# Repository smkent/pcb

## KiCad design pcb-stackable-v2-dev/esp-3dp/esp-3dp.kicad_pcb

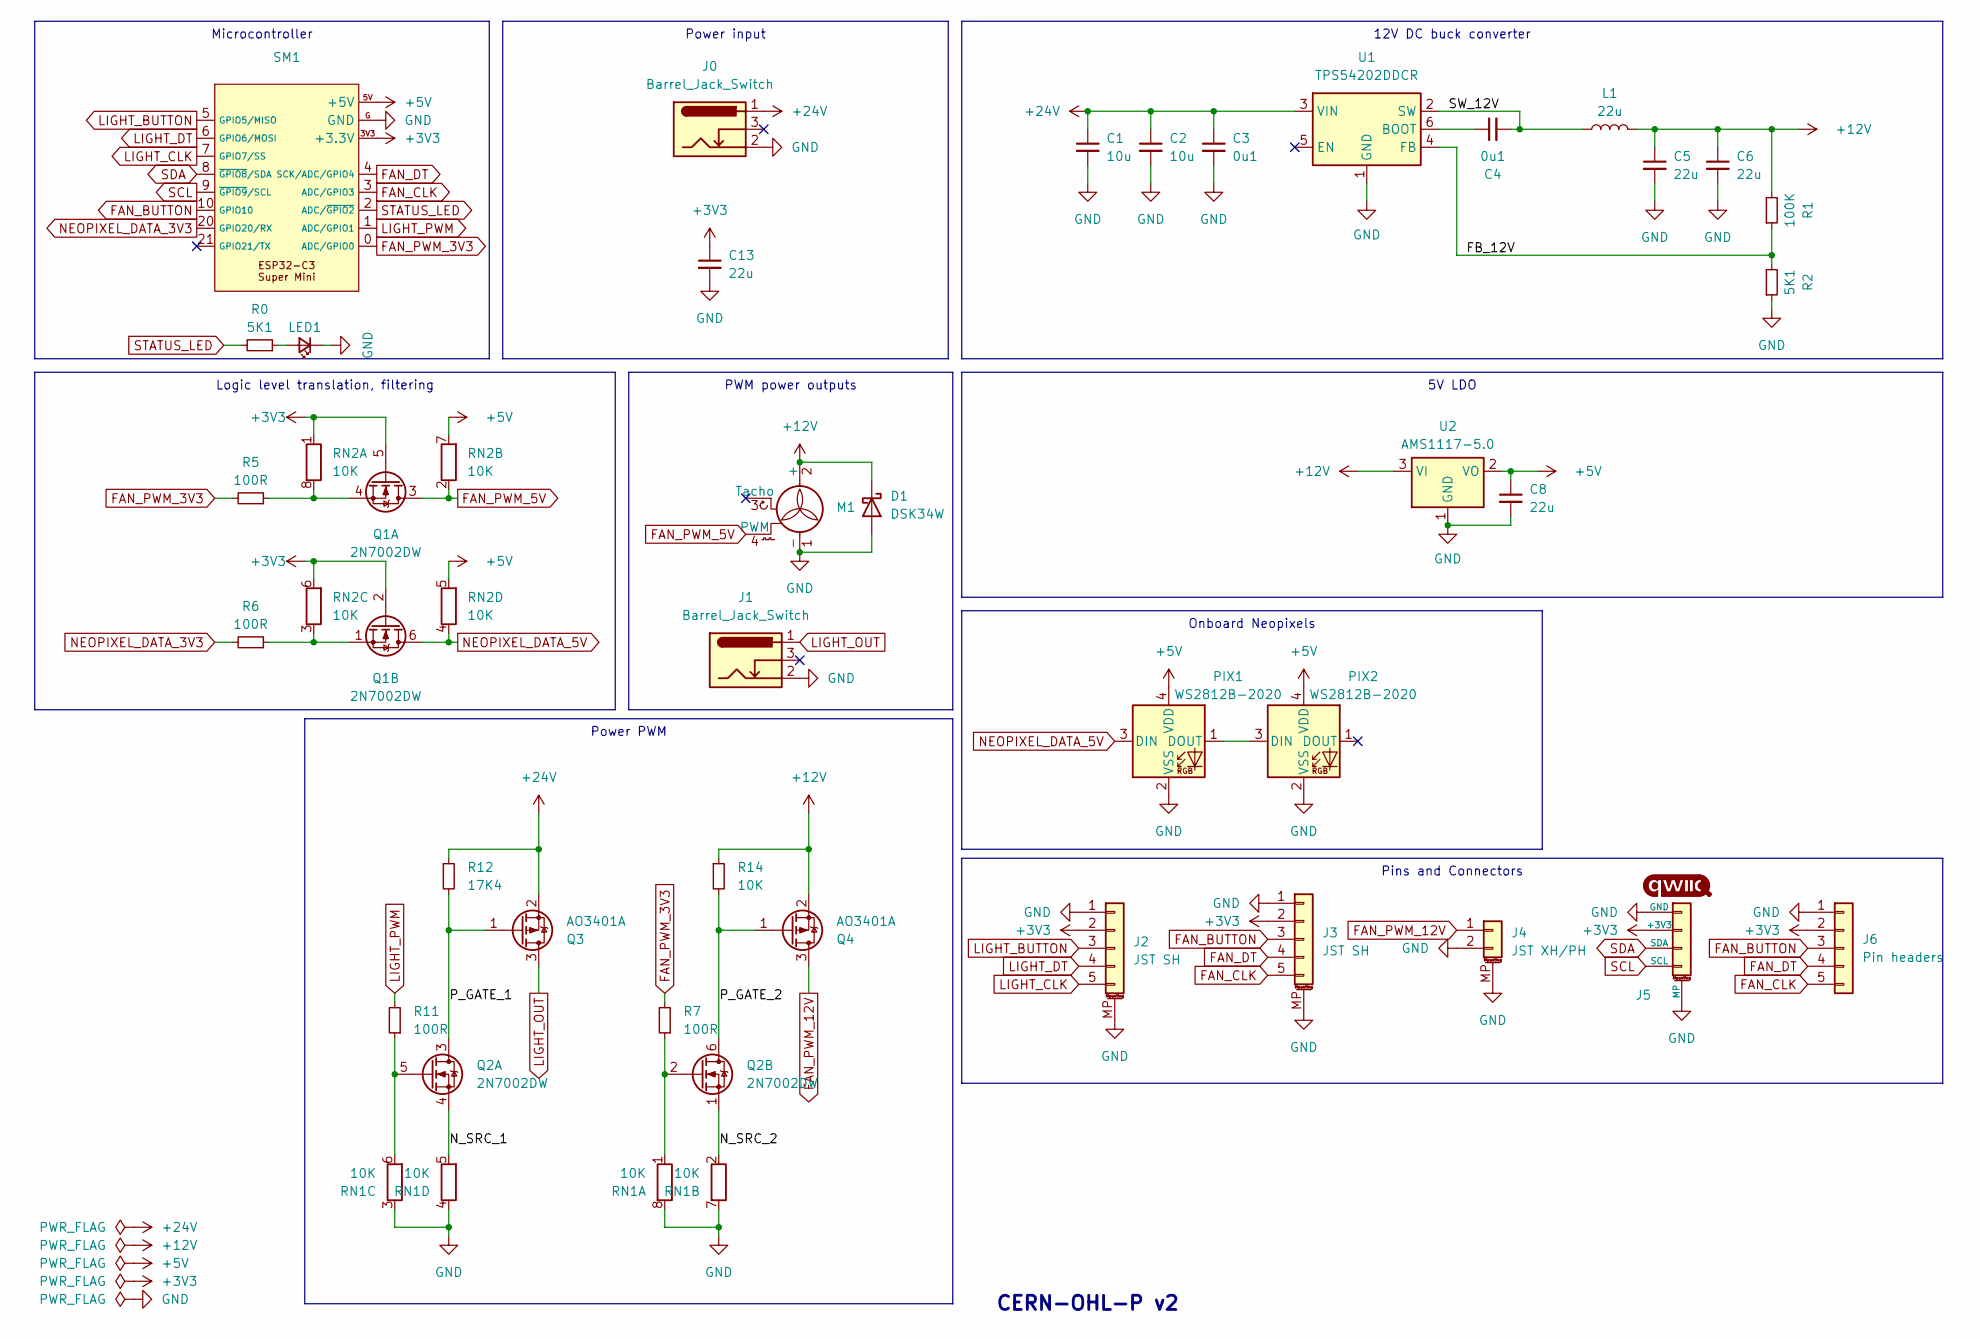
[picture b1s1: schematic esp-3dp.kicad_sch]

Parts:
C1, C2: 10u; C_0603_1608Metric_Pad1.08x0.95mm_HandSolder
C3, C4: 0u1; C_0603_1608Metric_Pad1.08x0.95mm_HandSolder
C5, C6, C8: 22u; C_0805_2012Metric_Pad1.18x1.45mm_HandSolder
C13: 22u; C_0603_1608Metric_Pad1.08x0.95mm_HandSolder
D1: DSK34W; D_SOD-123F_simple
J0, J1: Barrel_Jack_Switch; DC-IN_DC-050-2.0-BB_rev2
J2, J3: JST SH; JST_SH_SM05B-SRSS-TB_1x05-1MP_P1.00mm_Horizontal
J4: JST XH/PH; Conn_Combo_JST-1x02-XH_PH-SMD-pad2gnd
J5: Qwiic; Qwiic-SMD-horizontal-logo-bottom-pinout
J6: Pin headers; PinHeader_1x05_P2.54mm_Vertical_simple_pad1gnd
L1: 22u; IND-SMD_L7.0-W6.6; LCSC Part C22471106
LED1: LED_Small; LED_0603_1608Metric_Pad1.05x0.95mm_HandSolder_simple
M1: KF2510; FanPinHeader_1x04_P2.54mm_Horizontal
PIX1, PIX2: WS2812B-2020; LED-SMD_4P-L2.0-W2.0-BR-1
Q1, Q2: 2N7002DW; SOT-363_SC-70-6; LCSC Part C5190214
Q3, Q4: AO3401A; SOT-23
R0, R2: 5K1; R_0603_1608Metric_Pad0.98x0.95mm_HandSolder
R1: 100K; R_0603_1608Metric_Pad0.98x0.95mm_HandSolder
R5, R6, R7, R11: 100R; R_0603_1608Metric_Pad0.98x0.95mm_HandSolder
R12: 17K4; R_0603_1608Metric_Pad0.98x0.95mm_HandSolder
R14: 10K; R_0603_1608Metric_Pad0.98x0.95mm_HandSolder
RN1, RN2: 10K; R_Array_Convex_4x0603
SM1: ESP32-C3-Super-Mini-Castellated-SMD-only
U1: TPS54202DDCR; SOT-23-6; LCSC Part C191884
U2: AMS1117-5.0; SOT-223-3_TabPin2

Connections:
+3V3: C13.1, J2.2, J3.2, J5.2 (+3V3), J6.2, Q1.2 (G), Q1.5 (G), RN2.1 (R1.1), RN2.6 (R3.2), SM1.3V3 (+3.3V)
+5V: C8.1, PIX1.4 (VDD), PIX2.4 (VDD), RN2.5 (R4.2), RN2.7 (R2.2), SM1.5V (+5V), U2.2 (VO)
+12V: C5.1, C6.1, D1.1 (K), L1.2, M1.2 (+), Q4.2 (S), R1.2, R14.1, U2.3 (VI)
+24V: C1.1, C2.1, C3.1, J0.1, Q3.2 (S), R12.1, U1.3 (VIN)
/FB_12V: R1.1, R2.2, U1.4 (FB)
/N_SRC_1: Q2.4 (S), RN1.5 (R4.2)
/N_SRC_2: Q2.1 (S), RN1.2 (R2.1)
/P_GATE_1: Q2.3 (D), Q3.1 (G), R12.2
/P_GATE_2: Q2.6 (D), Q4.1 (G), R14.2
/SW_12V: C4.2, L1.1, U1.2 (SW)
FAN_BUTTON: J3.3, J6.3, SM1.10 (GPIO10)
FAN_CLK: J3.5, J6.5, SM1.3 (ADC/GPIO3)
FAN_DT: J3.4, J6.4, SM1.4 (SCK/ADC/GPIO4)
FAN_PWM_3V3: R5.2, R7.2, SM1.0 (ADC/GPIO0)
FAN_PWM_5V: M1.4 (PWM), Q1.3 (D), RN2.2 (R2.1)
FAN_PWM_12V: J4.1, Q4.3 (D)
GND: C1.2, C2.2, C3.2, C5.2, C6.2, C8.2, C13.2, D1.2 (A), J0.2, J1.2, J2.1, J2.MP (MountPin), J3.1, J3.MP (MountPin), J4.2, J4.MP (MountPin), J5.1 (GND), J5.MP, J6.1, LED1.1 (K), M1.1 (-), PIX1.2 (VSS), PIX2.2 (VSS), R2.1, RN1.3 (R3.1), RN1.4 (R4.1), RN1.7 (R2.2), RN1.8 (R1.2), SM1.G (GND), U1.1 (GND), U2.1 (GND)
LIGHT_BUTTON: J2.3, SM1.5 (GPIO5/MISO)
LIGHT_CLK: J2.5, SM1.7 (GPIO7/SS)
LIGHT_DT: J2.4, SM1.6 (GPIO6/MOSI)
LIGHT_OUT: J1.1, Q3.3 (D)
LIGHT_PWM: R11.2, SM1.1 (ADC/GPIO1)
NEOPIXEL_DATA_3V3: R6.2, SM1.20 (GPIO20/RX)
NEOPIXEL_DATA_5V: PIX1.3 (DIN), Q1.6 (D), RN2.4 (R4.1)
unnamed: LED1.2 (A), R0.1
unnamed: PIX1.1 (DOUT), PIX2.3 (DIN)
unnamed: Q1.4 (S), R5.1, RN2.8 (R1.2)
unnamed: Q1.1 (S), R6.1, RN2.3 (R3.1)
unnamed: Q2.5 (G), R11.1, RN1.6 (R3.2)
unnamed: Q2.2 (G), R7.1, RN1.1 (R1.1)
unnamed: C4.1, U1.6 (BOOT)
SCL: J5.4 (SCL), SM1.9 (~GPIO9/SCL)
SDA: J5.3 (SDA), SM1.8 (~GPIO8/SDA)
STATUS_LED: R0.2, SM1.2 (ADC/~GPIO2)

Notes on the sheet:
Power input
12V DC buck converter
5V LDO
Microcontroller
PWM power outputs
Onboard Neopixels
Pins and Connectors
Logic level translation, filtering
Power PWM
CERN-OHL-P v2

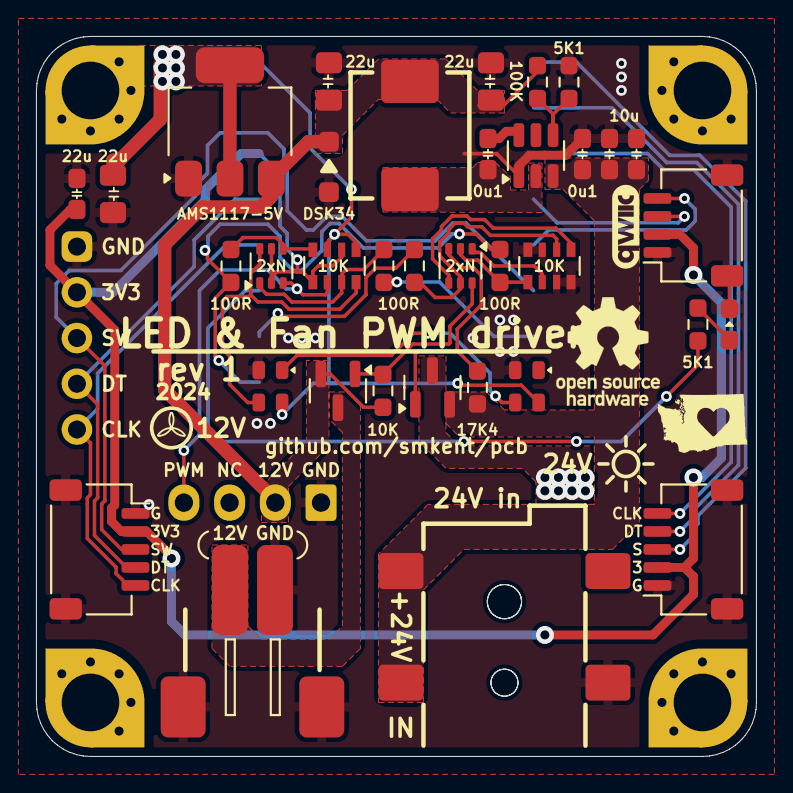
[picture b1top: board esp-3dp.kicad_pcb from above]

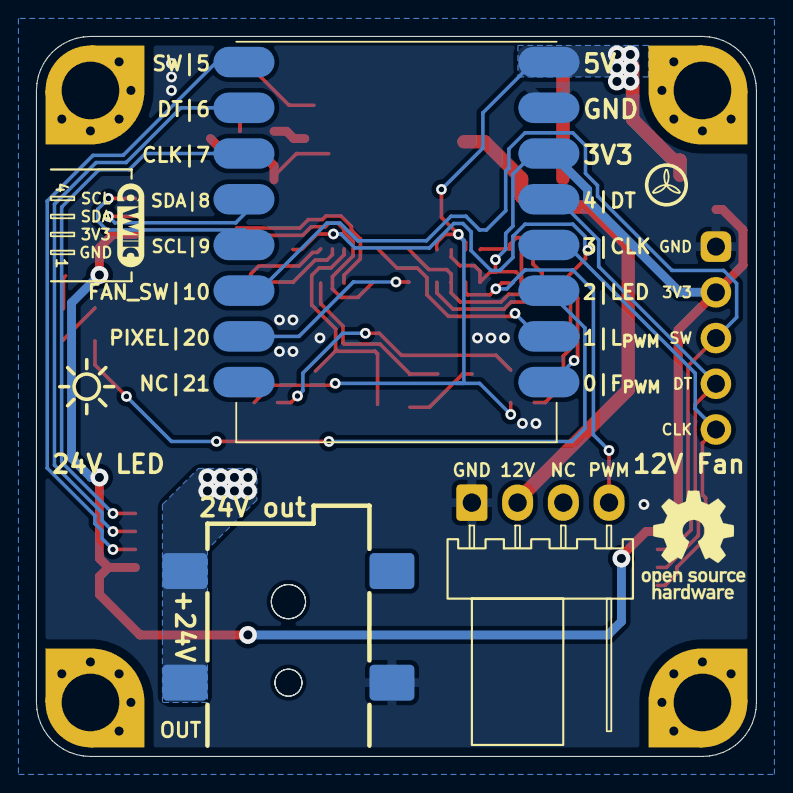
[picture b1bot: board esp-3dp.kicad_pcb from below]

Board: 2 copper layers, 40.0 x 40.0 mm, 43 parts (4 on the bottom side), 34 nets.

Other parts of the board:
MH_NE: MountingHole_3.2mm_M3_Pad_Via_corner_compact
MH_NW: MountingHole_3.2mm_M3_Pad_Via_corner_compact
MH_SE: MountingHole_3.2mm_M3_Pad_Via_corner_compact
MH_SW: MountingHole_3.2mm_M3_Pad_Via_corner_compact

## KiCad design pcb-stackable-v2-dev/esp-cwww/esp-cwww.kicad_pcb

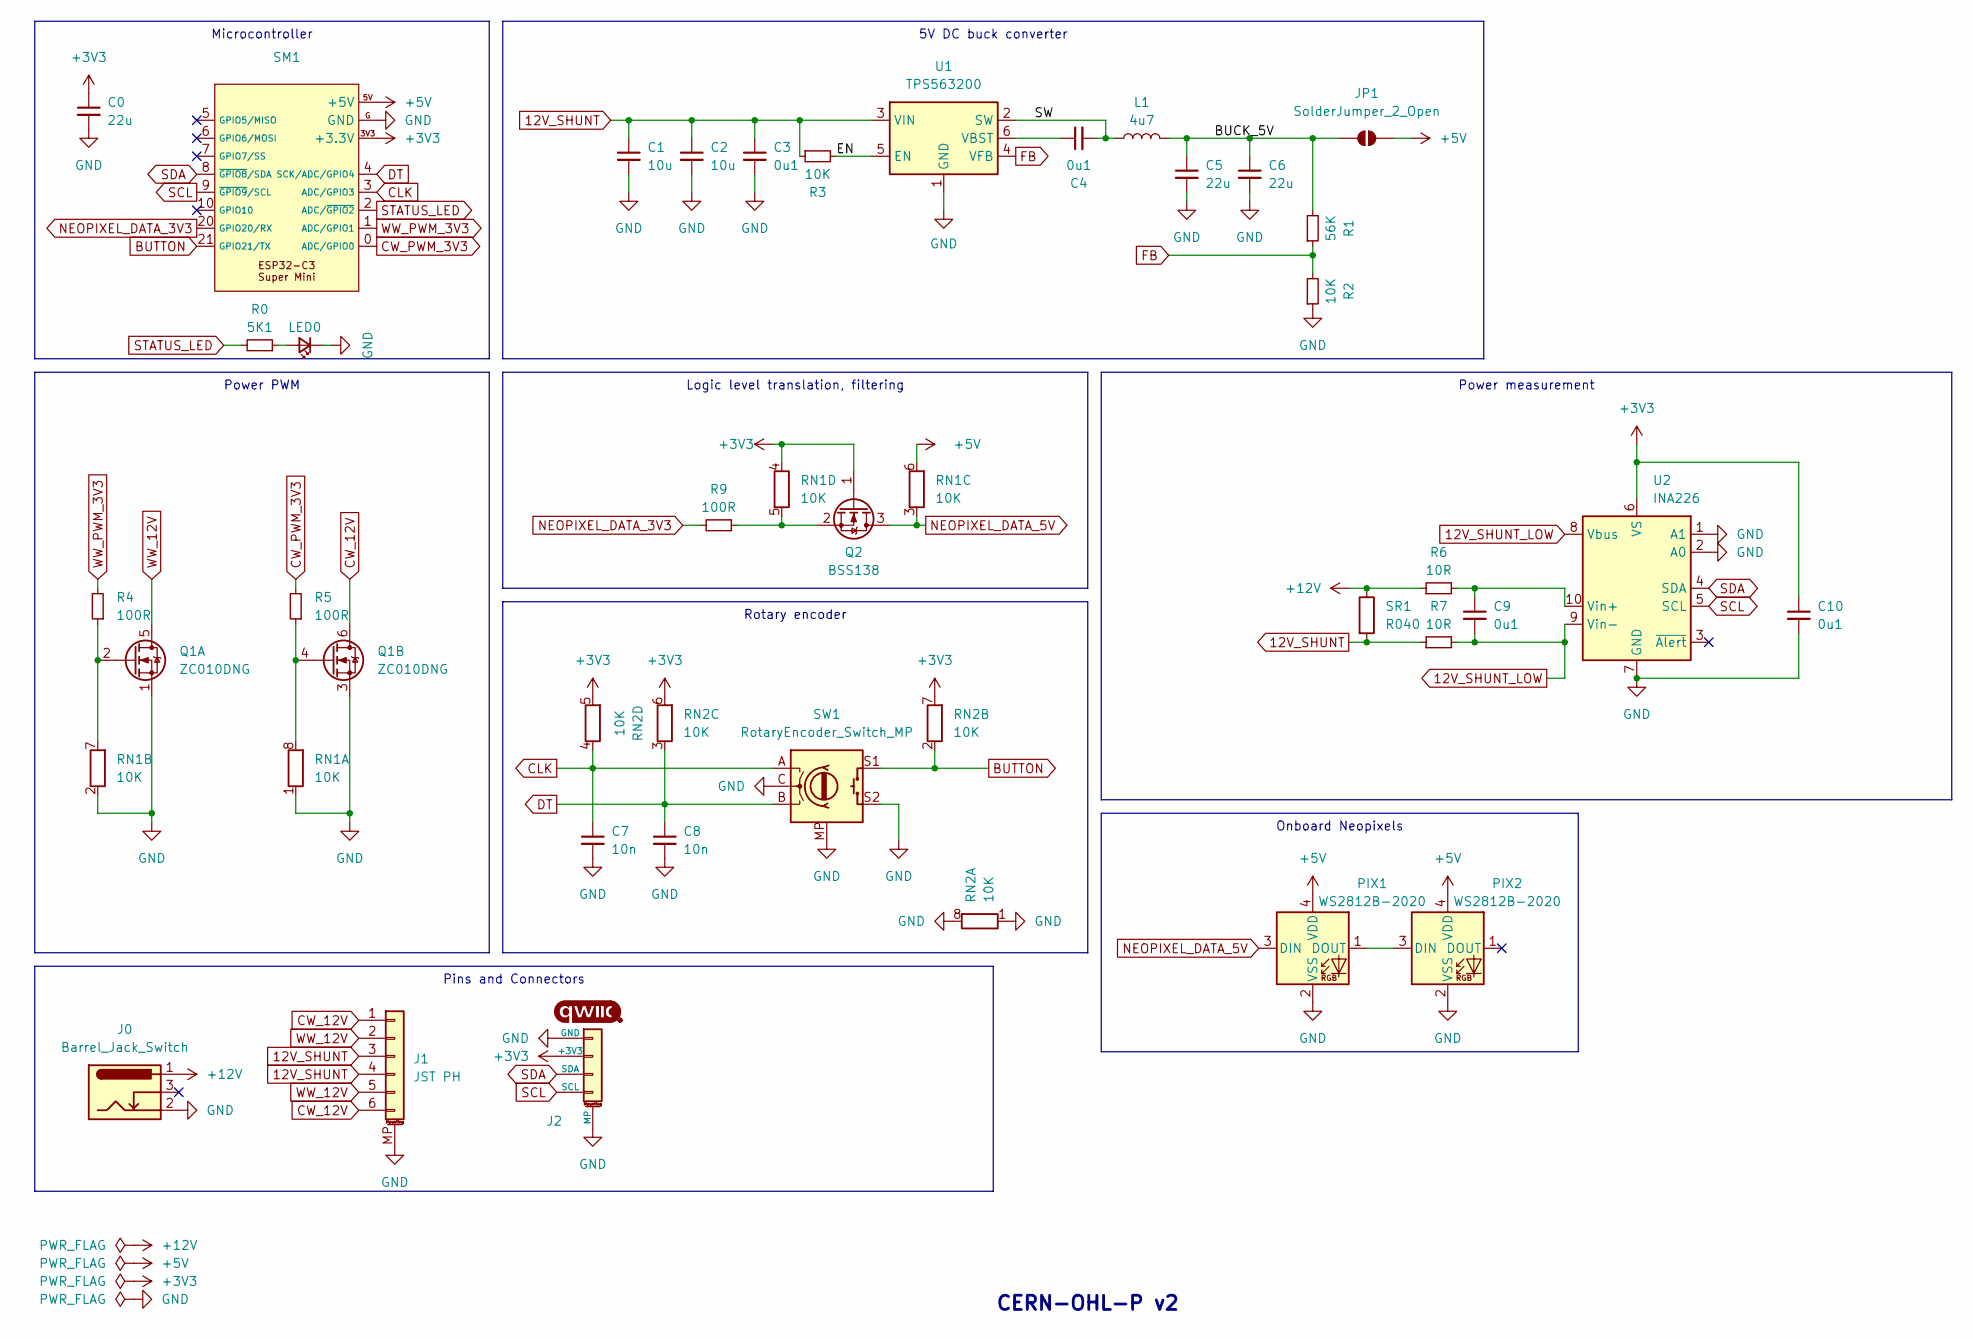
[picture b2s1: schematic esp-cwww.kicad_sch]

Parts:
C0, C5, C6: 22u; C_0603_1608Metric_Pad1.08x0.95mm_HandSolder
C1, C2: 10u; C_0603_1608Metric_Pad1.08x0.95mm_HandSolder
C3, C4: 0u1; C_0603_1608Metric_Pad1.08x0.95mm_HandSolder
C7, C8: 10n; C_0603_1608Metric_Pad1.08x0.95mm_HandSolder
C9, C10: 0u1; C_0402_1005Metric_simple; LCSC Part C1525
J0: Barrel_Jack_Switch; DC-IN_DC-050-2.0-BB_rev2
J1: JST PH; JST_PH_S6B-PH-SM4-TB_1x06-1MP_P2.00mm_Horizontal
J2: Qwiic; Qwiic-SMD-horizontal-logo
JP1: SolderJumper_2_Open; SolderJumper-2_P1.3mm_Open_TrianglePad1.0x1.5mm
L1: 4u7; IND-SMD_L2.5-W2.0_MHCHL2520
LED0: LED_Small; LED_0603_1608Metric_Pad1.05x0.95mm_HandSolder_simple
PIX1, PIX2: WS2812B-2020; LED-SK6812SIDE-A-4x1.6mm
Q1: ZC010DNG; PDFN-8_L3.2-W3.1-P0.65-LS3.4-BL-EP2; LCSC Part C36499170
Q2: BSS138; SOT-23_simple
R0: 5K1; R_0603_1608Metric_Pad0.98x0.95mm_HandSolder
R1: 56K; R_0603_1608Metric_Pad0.98x0.95mm_HandSolder
R2, R3: 10K; R_0603_1608Metric_Pad0.98x0.95mm_HandSolder
R4, R5, R9: 100R; R_0603_1608Metric_Pad0.98x0.95mm_HandSolder
R6: 10R; R_0402_1005Metric
R7: 10R; R_0402_1005Metric; LCSC Part C25077
RN1, RN2: 10K; R_Array_Convex_4x0603
SM1: ESP32-C3-Super-Mini-Castellated-SMD-only
SR1: R040; R_2512_6332Metric_Pad1.40x3.35mm_HandSolder; LCSC Part C2985725
SW1: RotaryEncoder_Switch_MP; RotaryEncoder_Alps_EC11-Switch_Combo_H20mm
U1: TPS563200; SOT-23-6_Handsoldering_simple
U2: INA226; VSSOP-10_3x3mm_P0.5mm

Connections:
12V_SHUNT: C1.1, C2.1, C3.1, J1.3, J1.4, R3.1, R7.1, SR1.2, U1.3 (VIN)
12V_SHUNT_LOW: C9.2, R7.2, U2.8 (Vbus), U2.9 (Vin-)
+3V3: C0.1, C10.1, J2.2 (+3V3), Q2.1 (G), RN1.4 (R4.1), RN2.5 (R4.2), RN2.6 (R3.2), RN2.7 (R2.2), SM1.3V3 (+3.3V), U2.6 (VS)
+5V: JP1.2 (B), PIX1.4 (VDD), PIX2.4 (VDD), RN1.6 (R3.2), SM1.5V (+5V)
+12V: J0.1, R6.1, SR1.1
/BUCK_5V: C5.1, C6.1, JP1.1 (A), L1.2, R1.2
/EN: R3.2, U1.5 (EN)
/SW: C4.2, L1.1, U1.2 (SW)
BUTTON: RN2.2 (R2.1), SM1.21 (GPIO21/TX), SW1.S1
CLK: C7.1, RN2.4 (R4.1), SM1.3 (ADC/GPIO3), SW1.A
CW_12V: J1.1, J1.6, Q1.6 (D)
CW_PWM_3V3: R5.2, SM1.0 (ADC/GPIO0)
DT: C8.1, RN2.3 (R3.1), SM1.4 (SCK/ADC/GPIO4), SW1.B
FB: R1.1, R2.2, U1.4 (VFB)
GND: C0.2, C1.2, C2.2, C3.2, C5.2, C6.2, C7.2, C8.2, C10.2, J0.2, J1.MP (MountPin), J2.1 (GND), J2.MP, LED0.1 (K), PIX1.2 (VSS), PIX2.2 (VSS), Q1.1 (S), Q1.3 (S), R2.1, RN1.1 (R1.1), RN1.2 (R2.1), RN2.1 (R1.1), RN2.8 (R1.2), SM1.G (GND), SW1.C, SW1.MP, SW1.S2, U1.1 (GND), U2.1 (A1), U2.2 (A0), U2.7 (GND)
NEOPIXEL_DATA_3V3: R9.2, SM1.20 (GPIO20/RX)
NEOPIXEL_DATA_5V: PIX1.3 (DIN), Q2.3 (D), RN1.3 (R3.1)
unnamed: LED0.2 (A), R0.1
unnamed: PIX1.1 (DOUT), PIX2.3 (DIN)
unnamed: Q1.2 (G), R4.1, RN1.7 (R2.2)
unnamed: Q1.4 (G), R5.1, RN1.8 (R1.2)
unnamed: Q2.2 (S), R9.1, RN1.5 (R4.2)
unnamed: C4.1, U1.6 (VBST)
unnamed: C9.1, R6.2, U2.10 (Vin+)
SCL: J2.4 (SCL), SM1.9 (~GPIO9/SCL), U2.5 (SCL)
SDA: J2.3 (SDA), SM1.8 (~GPIO8/SDA), U2.4 (SDA)
STATUS_LED: R0.2, SM1.2 (ADC/~GPIO2)
WW_12V: J1.2, J1.5, Q1.5 (D)
WW_PWM_3V3: R4.2, SM1.1 (ADC/GPIO1)

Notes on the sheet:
Rotary encoder
5V DC buck converter
Onboard Neopixels
Logic level translation, filtering
Power PWM
Power measurement
Pins and Connectors
Microcontroller
CERN-OHL-P v2

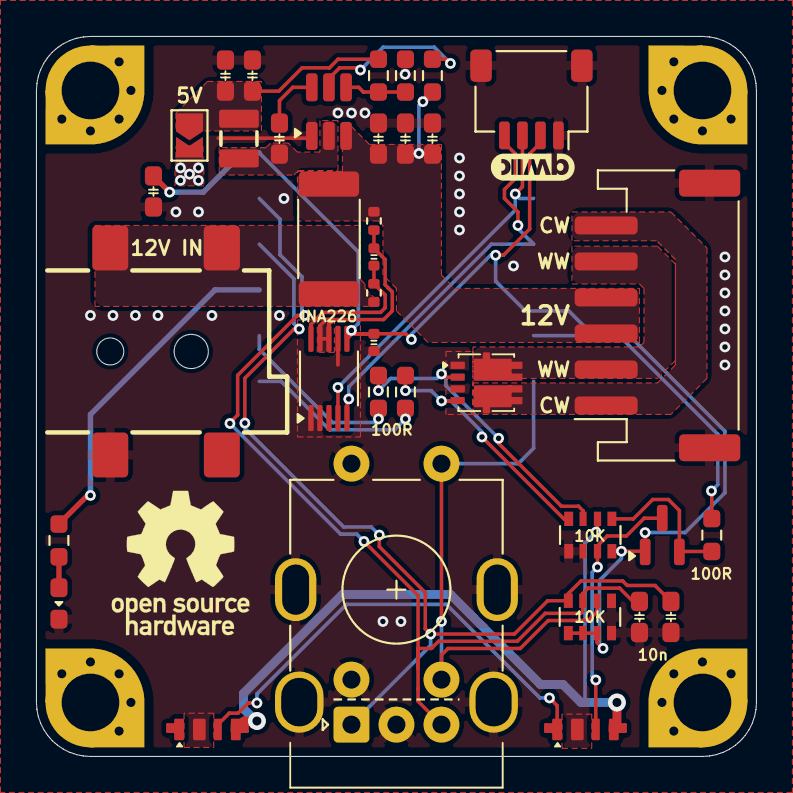
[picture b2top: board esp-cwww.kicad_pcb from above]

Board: 2 copper layers, 40.0 x 40.0 mm, 37 parts (1 on the bottom side), 29 nets.

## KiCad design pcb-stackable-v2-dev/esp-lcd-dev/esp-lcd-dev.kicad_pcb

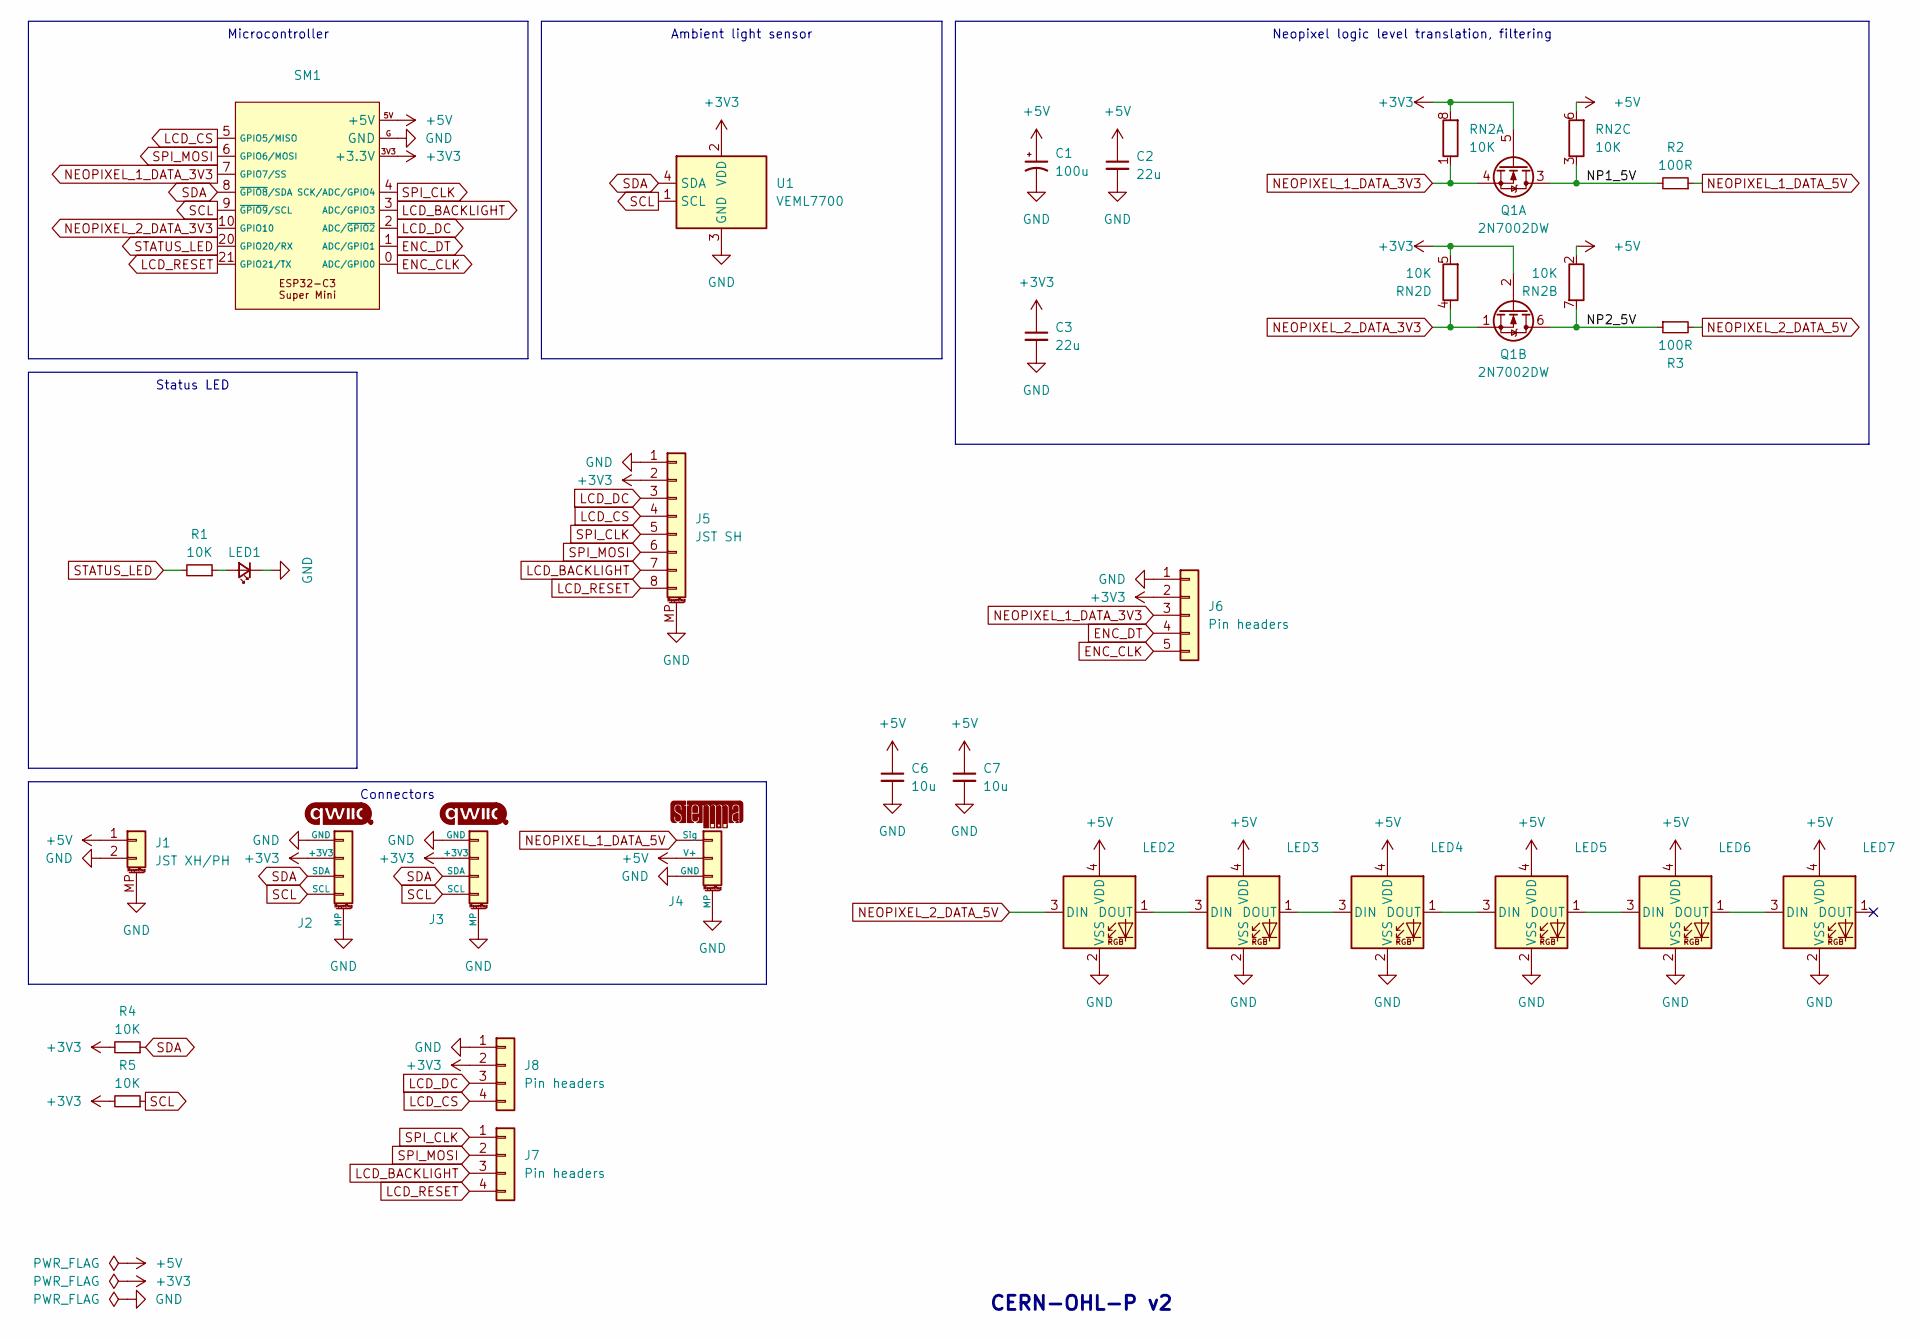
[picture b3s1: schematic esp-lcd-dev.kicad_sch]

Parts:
C1: 100u; CP_Elec_5x5.4
C2, C3: 22u; C_0603_1608Metric_Pad1.08x0.95mm_HandSolder
C6, C7: 10u; C_0603_1608Metric_Pad1.08x0.95mm_HandSolder
J1: JST XH/PH; Conn_Combo_JST-1x02-XH_PH-SMD-pad2gnd
J2, J3: Qwiic; Qwiic-SMD-horizontal-logo-bottom-pinout
J4: STEMMA-Signal; STEMMA-Signal-SMD-horizontal
J5: JST SH; JST_SH_SM08B-SRSS-TB_1x08-1MP_P1.00mm_Horizontal
J6: Pin headers; PinHeader_1x05_P2.54mm_Vertical_simple_pad1gnd
J7: Pin headers; PinSocket_1x04_P2.54mm_Vertical_SMD_Pin1Right
J8: Pin headers; PinSocket_1x04_P2.54mm_Vertical_SMD_Pin1Left
LED1: LED_Small; LED_0603_1608Metric_Pad1.05x0.95mm_HandSolder_simple
LED2, LED3, LED4, LED5, LED6, LED7: WS2812B-2020; LED-SMD_4P-L2.0-W2.0-BR-1
Q1: 2N7002DW; SOT-363_SC-70-6; LCSC Part C5190214
R1, R4, R5: 10K; R_0603_1608Metric_Pad0.98x0.95mm_HandSolder
R2, R3: 100R; R_0603_1608Metric_Pad0.98x0.95mm_HandSolder
RN2: 10K; R_Array_Convex_4x0603
SM1: ESP32-C3-Super-Mini-Castellated-SMD-only
U1: VEML7700; SENSORS-SMD_VEML7700-TR

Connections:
+3V3: C3.1, J2.2 (+3V3), J3.2 (+3V3), J5.2, J6.2, J8.2, Q1.2 (G), Q1.5 (G), R4.2, R5.2, RN2.5 (R4.2), RN2.8 (R1.2), SM1.3V3 (+3.3V), U1.2 (VDD)
+5V: C1.1, C2.1, C6.1, C7.1, J1.1, J4.2 (V+), LED2.4 (VDD), LED3.4 (VDD), LED4.4 (VDD), LED5.4 (VDD), LED6.4 (VDD), LED7.4 (VDD), RN2.2 (R2.1), RN2.6 (R3.2), SM1.5V (+5V)
/NP1_5V: Q1.3 (D), R2.2, RN2.3 (R3.1)
/NP2_5V: Q1.6 (D), R3.1, RN2.7 (R2.2)
ENC_CLK: J6.5, SM1.0 (ADC/GPIO0)
ENC_DT: J6.4, SM1.1 (ADC/GPIO1)
GND: C1.2, C2.2, C3.2, C6.2, C7.2, J1.2, J1.MP (MountPin), J2.1 (GND), J2.MP, J3.1 (GND), J3.MP, J4.3 (GND), J4.MP, J5.1, J5.MP (MountPin), J6.1, J8.1, LED1.1 (K), LED2.2 (VSS), LED3.2 (VSS), LED4.2 (VSS), LED5.2 (VSS), LED6.2 (VSS), LED7.2 (VSS), SM1.G (GND), U1.3 (GND)
LCD_BACKLIGHT: J5.7, J7.3, SM1.3 (ADC/GPIO3)
LCD_CS: J5.4, J8.4, SM1.5 (GPIO5/MISO)
LCD_DC: J5.3, J8.3, SM1.2 (ADC/~GPIO2)
LCD_RESET: J5.8, J7.4, SM1.21 (GPIO21/TX)
NEOPIXEL_1_DATA_3V3: J6.3, Q1.4 (S), RN2.1 (R1.1), SM1.7 (GPIO7/SS)
NEOPIXEL_1_DATA_5V: J4.1 (Sig), R2.1
NEOPIXEL_2_DATA_3V3: Q1.1 (S), RN2.4 (R4.1), SM1.10 (GPIO10)
NEOPIXEL_2_DATA_5V: LED2.3 (DIN), R3.2
unnamed: LED1.2 (A), R1.1
unnamed: LED2.1 (DOUT), LED3.3 (DIN)
unnamed: LED3.1 (DOUT), LED4.3 (DIN)
unnamed: LED4.1 (DOUT), LED5.3 (DIN)
unnamed: LED5.1 (DOUT), LED6.3 (DIN)
unnamed: LED6.1 (DOUT), LED7.3 (DIN)
SCL: J2.4 (SCL), J3.4 (SCL), R5.1, SM1.9 (~GPIO9/SCL), U1.1 (SCL)
SDA: J2.3 (SDA), J3.3 (SDA), R4.1, SM1.8 (~GPIO8/SDA), U1.4 (SDA)
SPI_CLK: J5.5, J7.1, SM1.4 (SCK/ADC/GPIO4)
SPI_MOSI: J5.6, J7.2, SM1.6 (GPIO6/MOSI)
STATUS_LED: R1.2, SM1.20 (GPIO20/RX)

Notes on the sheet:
Neopixel logic level translation, filtering
Connectors
Status LED
Ambient light sensor
Microcontroller
CERN-OHL-P v2

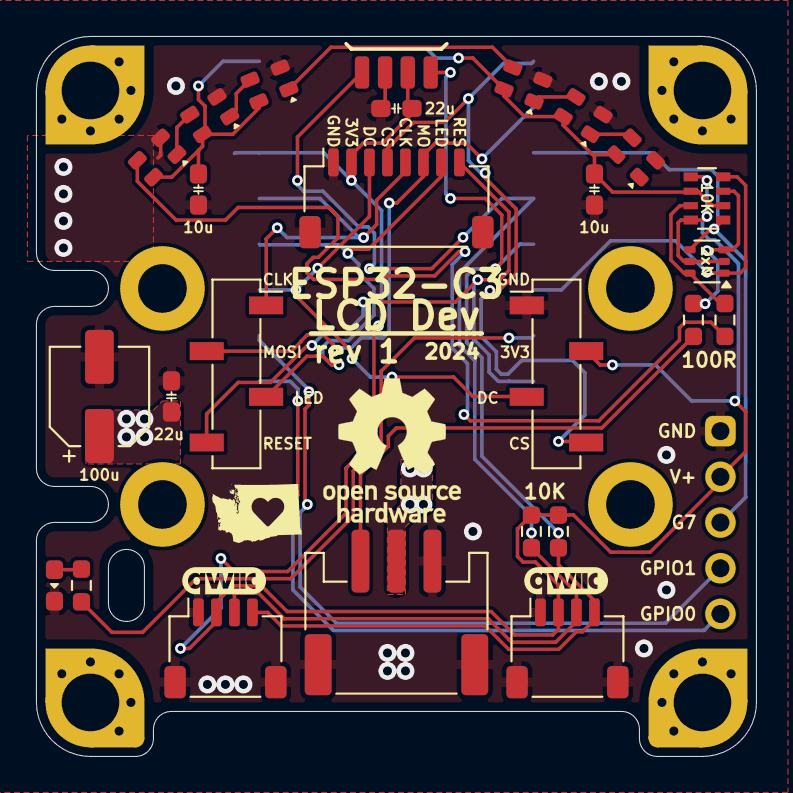
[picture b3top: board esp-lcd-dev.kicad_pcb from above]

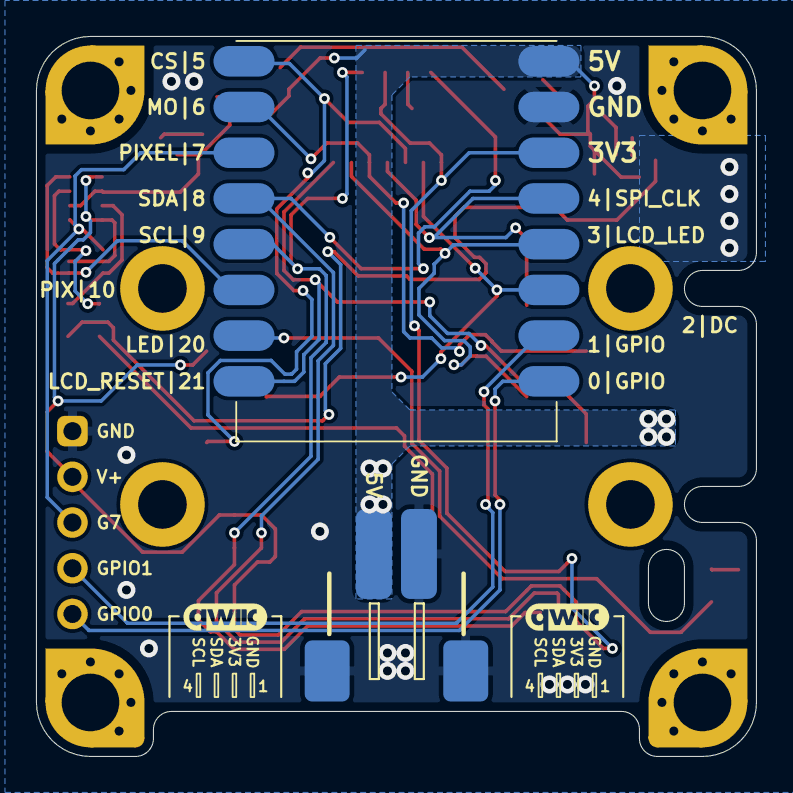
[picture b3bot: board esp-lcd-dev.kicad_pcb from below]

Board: 2 copper layers, 40.0 x 40.0 mm, 29 parts (3 on the bottom side), 26 nets.

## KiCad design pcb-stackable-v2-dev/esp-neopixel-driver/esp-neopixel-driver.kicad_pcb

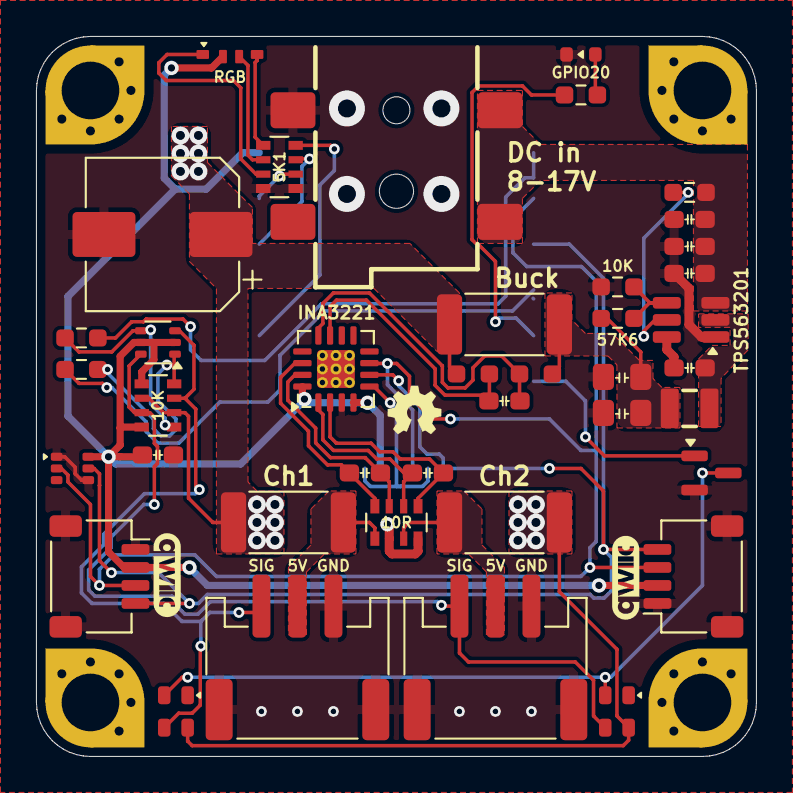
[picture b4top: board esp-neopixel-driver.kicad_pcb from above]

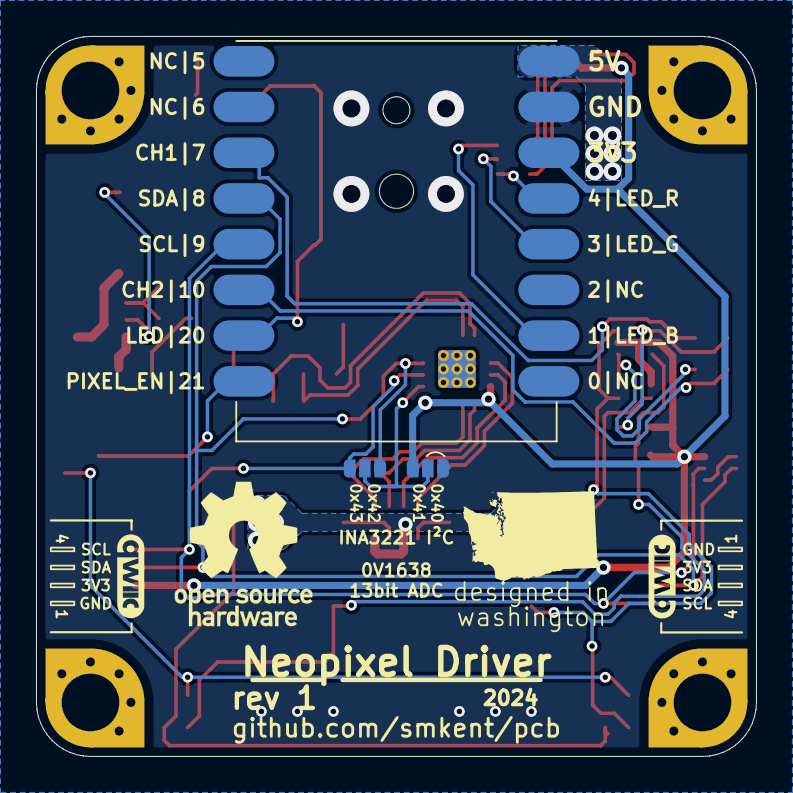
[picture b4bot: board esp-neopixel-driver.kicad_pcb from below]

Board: 2 copper layers, 40.0 x 40.0 mm, 47 parts (3 on the bottom side), 36 nets.

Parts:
C1, C2: 10u; C_0603_1608Metric_Pad1.08x0.95mm_HandSolder
C3, C4, C8, C9, C10: 0u1; C_0603_1608Metric_Pad1.08x0.95mm_HandSolder
C5, C6: 22u; C_0805_2012Metric_Pad1.18x1.45mm_HandSolder
C7: 22u; C_0603_1608Metric_Pad1.08x0.95mm_HandSolder
C11: 1000u; CP_Elec_8x10
J1, J2: STEMMA-Signal; STEMMA-Signal-SMD-horizontal
J3, J4: Qwiic; Qwiic-SMD-horizontal-logo-bottom-pinout
J7: Barrel_Jack_Switch; DC-IN_DC-050-2.0-BB_rev2
JP1: VS/GND; SolderJumper-3_P1.0mm_Open_RoundedPad_simple
JP2: SDA/SCL; SolderJumper-3_P1.0mm_Open_RoundedPad_simple
L1: 4u7; IND-SMD_L2.5-W2.0_MHCHL2520
LED0: LED_Small; LED-SMD_L1.7-W1.1-R-RD_BLUE
LED1, LED2: WS2812B-2020; LED-SMD_4P-L2.0-W2.0-BR-1
LED3: FM-3510RGBA-SG; LED-SMD_FM-3510RGBA-SG
MH_NE: MountingHole_3.2mm_M3_Pad_Via_corner_compact
MH_NW: MountingHole_3.2mm_M3_Pad_Via_corner_compact
MH_SE: MountingHole_3.2mm_M3_Pad_Via_corner_compact
MH_SW: MountingHole_3.2mm_M3_Pad_Via_corner_compact
Q1: BSS138; SOT-23_simple
Q2: 2N7002DW; SOT-363_SC-70-6
R1, R2, R4: 10K; R_0603_1608Metric_Pad0.98x0.95mm_HandSolder
R3: 56K; R_0603_1608Metric_Pad0.98x0.95mm_HandSolder
R5, R6: 10R; R_0603_1608Metric_Pad0.98x0.95mm_HandSolder_simple
R7, R8: 300R; R_0603_1608Metric_Pad0.98x0.95mm_HandSolder
RN1: 10K; R_Array_Convex_4x0603
RN2: 10R; R_Array_Convex_4x0603
RN3: 5K1; R_Array_Convex_4x0603
SM1: ESP32-C3-Super-Mini-Castellated-SMD-only
SR1, SR2, SR3: R040; R_2512_6332Metric_Pad1.40x3.35mm_HandSolder
U1: TPS563201; SOT-23-6_Handsoldering_simple
U2: INA3221; Texas_RGV0016A_VQFN-16-1EP_4x4mm_P0.65mm_EP2.1x2.1mm_Therma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
U3: VEML6030; SENSORS-SMD_VEML6030

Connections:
5V_SHUNT: C5.1, C6.1, L1.2, R3.2, R5.1, SR1.1
+3V3: C7.1, J3.2 (+3V3), J4.2 (+3V3), JP1.1 (A), LED3.2 (A), Q2.2 (G), Q2.5 (G), RN1.5 (R4.2), RN1.8 (R1.2), SM1.3V3 (+3.3V), U2.4 (VS), U2.16 (VPU), U3.6 (VDD)
+5V: C11.1, LED1.4 (VDD), LED2.4 (VDD), R6.1, RN1.2 (R2.1), RN1.6 (R3.2), RN2.2 (R2.1), RN2.4 (R4.1), SM1.5V (+5V), SR1.2, SR2.2, SR3.2
DC_IN: C1.1, C2.1, C3.1, J7.1, R2.1, U1.3 (VIN)
FB: R3.1, R4.2, U1.4 (VFB)
GND: C1.2, C2.2, C3.2, C5.2, C6.2, C7.2, C11.2, J1.3 (GND), J1.MP, J2.3 (GND), J2.MP, J3.1 (GND), J3.MP, J4.1 (GND), J4.MP, J7.2, JP1.3 (B), LED0.1 (K), Q1.2 (S), R4.1, RN3.4 (R4.1), RN3.5 (R4.2), SM1.G (GND), U1.1 (GND), U2.3 (GND), U3.1 (GND), U3.4 (ADD)
LED_B: RN3.8 (R1.2), SM1.1 (ADC/GPIO1)
LED_G: RN3.7 (R2.2), SM1.3 (ADC/GPIO3)
LED_R: RN3.6 (R3.2), SM1.4 (SCK/ADC/GPIO4)
NEOPIXEL_1_DATA_3V3: R7.2, SM1.7 (GPIO7/SS)
NEOPIXEL_1_DATA_5V: J1.1 (Sig), LED1.3 (DIN), Q2.3 (D), RN1.3 (R3.1)
NEOPIXEL_1_SHUNT: J1.2 (V+), RN2.1 (R1.1), SR2.1
NEOPIXEL_2_DATA_3V3: R8.1, SM1.10 (GPIO10)
NEOPIXEL_2_DATA_5V: J2.1 (Sig), LED2.3 (DIN), Q2.6 (D), RN1.7 (R2.2)
NEOPIXEL_2_SHUNT: J2.2 (V+), RN2.3 (R3.1), SR3.1
unnamed: JP1.2 (C), JP2.2 (C), U2.5 (A0)
unnamed: LED0.2 (A), R1.1
unnamed: LED3.4 (BK), RN3.1 (R1.1)
unnamed: LED3.3 (GK), RN3.2 (R2.1)
unnamed: LED3.1 (RK), RN3.3 (R3.1)
unnamed: Q2.4 (S), R7.1, RN1.1 (R1.1)
unnamed: Q2.1 (S), R8.2, RN1.4 (R4.1)
unnamed: C9.2, RN2.8 (R1.2), U2.14 (IN-2)
unnamed: C9.1, RN2.7 (R2.2), U2.15 (IN+2)
unnamed: C10.2, RN2.6 (R3.2), U2.1 (IN-3)
unnamed: C10.1, RN2.5 (R4.2), U2.2 (IN+3)
unnamed: R2.2, U1.5 (EN)
unnamed: C4.1, U1.6 (VBST)
unnamed: C8.1, R5.2, U2.12 (IN+1)
unnamed: C8.2, R6.2, U2.11 (IN-1)
SCL: J3.4 (SCL), J4.4 (SCL), JP2.1 (A), SM1.9 (~GPIO9/SCL), U2.6 (SCL), U3.5 (SCL)
SDA: J3.3 (SDA), J4.3 (SDA), JP2.3 (B), SM1.8 (~GPIO8/SDA), U2.7 (SDA), U3.2 (SDA)
SMD_PIXEL_ENABLE: Q1.1 (G), SM1.21 (GPIO21/TX)
SMD_PIXEL_GND: LED1.2 (VSS), LED2.2 (VSS), Q1.3 (D)
STATUS_LED: R1.2, SM1.20 (GPIO20/RX)
SW: C4.2, L1.1, U1.2 (SW)

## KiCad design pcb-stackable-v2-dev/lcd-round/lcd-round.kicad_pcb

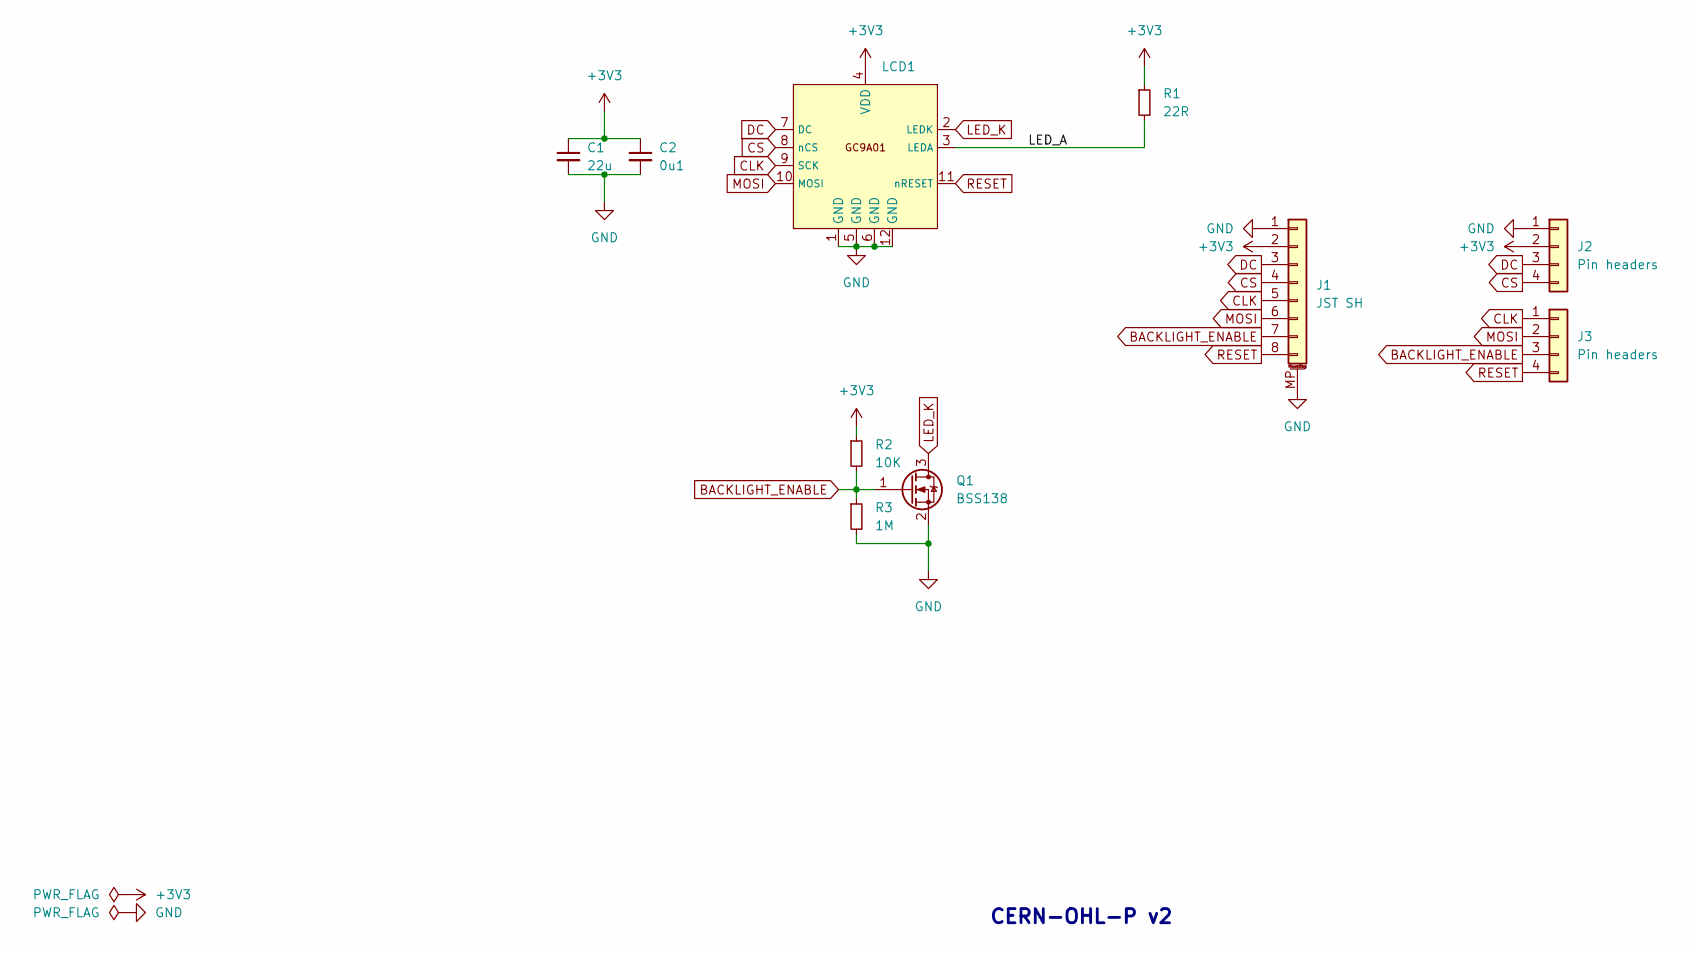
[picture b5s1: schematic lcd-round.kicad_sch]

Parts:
C1: 22u; C_0603_1608Metric_Pad1.08x0.95mm_HandSolder
C2: 0u1; C_0603_1608Metric_Pad1.08x0.95mm_HandSolder
J1: JST SH; JST_SH_SM08B-SRSS-TB_1x08-1MP_P1.00mm_Horizontal
J2: Pin headers; PinHeader_1x04_P2.54mm_Vertical_SMD_Pin1Right
J3: Pin headers; PinHeader_1x04_P2.54mm_Vertical_SMD_Pin1Left
LCD1: GC9A01; GC9A01-screen-connector-pads
Q1: BSS138; SOT-23_simple
R1: 22R; R_0603_1608Metric_Pad0.98x0.95mm_HandSolder_simple
R2: 10K; R_0603_1608Metric_Pad0.98x0.95mm_HandSolder_simple
R3: 1M; R_0603_1608Metric_Pad0.98x0.95mm_HandSolder_simple

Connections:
+3V3: C1.1, C2.1, J1.2, J2.2, LCD1.4 (VDD), R1.1, R2.1
/LED_A: LCD1.3 (LEDA), R1.2
BACKLIGHT_ENABLE: J1.7, J3.3, Q1.1 (G), R2.2, R3.1
CLK: J1.5, J3.1, LCD1.9 (SCK)
CS: J1.4, J2.4, LCD1.8 (nCS)
DC: J1.3, J2.3, LCD1.7 (DC)
GND: C1.2, C2.2, J1.1, J1.MP (MountPin), J2.1, LCD1.1 (GND), LCD1.5 (GND), LCD1.6 (GND), LCD1.12 (GND), Q1.2 (S), R3.2
LED_K: LCD1.2 (LEDK), Q1.3 (D)
MOSI: J1.6, J3.2, LCD1.10 (MOSI)
RESET: J1.8, J3.4, LCD1.11 (nRESET)

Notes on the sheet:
CERN-OHL-P v2
